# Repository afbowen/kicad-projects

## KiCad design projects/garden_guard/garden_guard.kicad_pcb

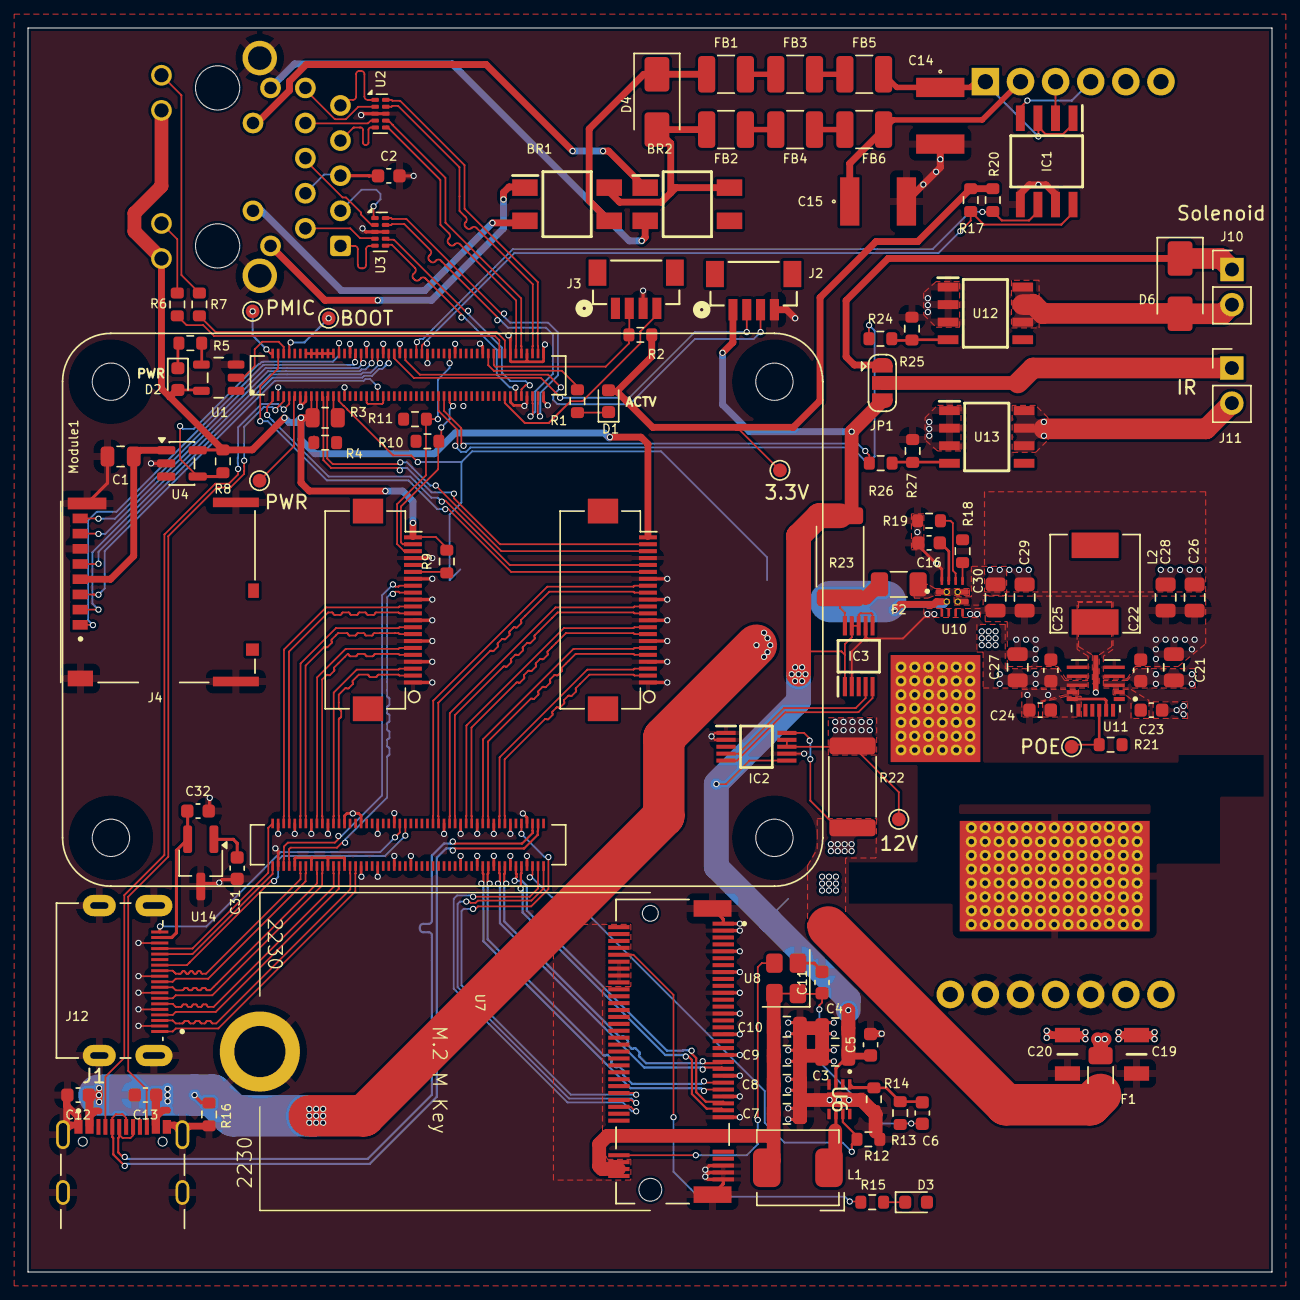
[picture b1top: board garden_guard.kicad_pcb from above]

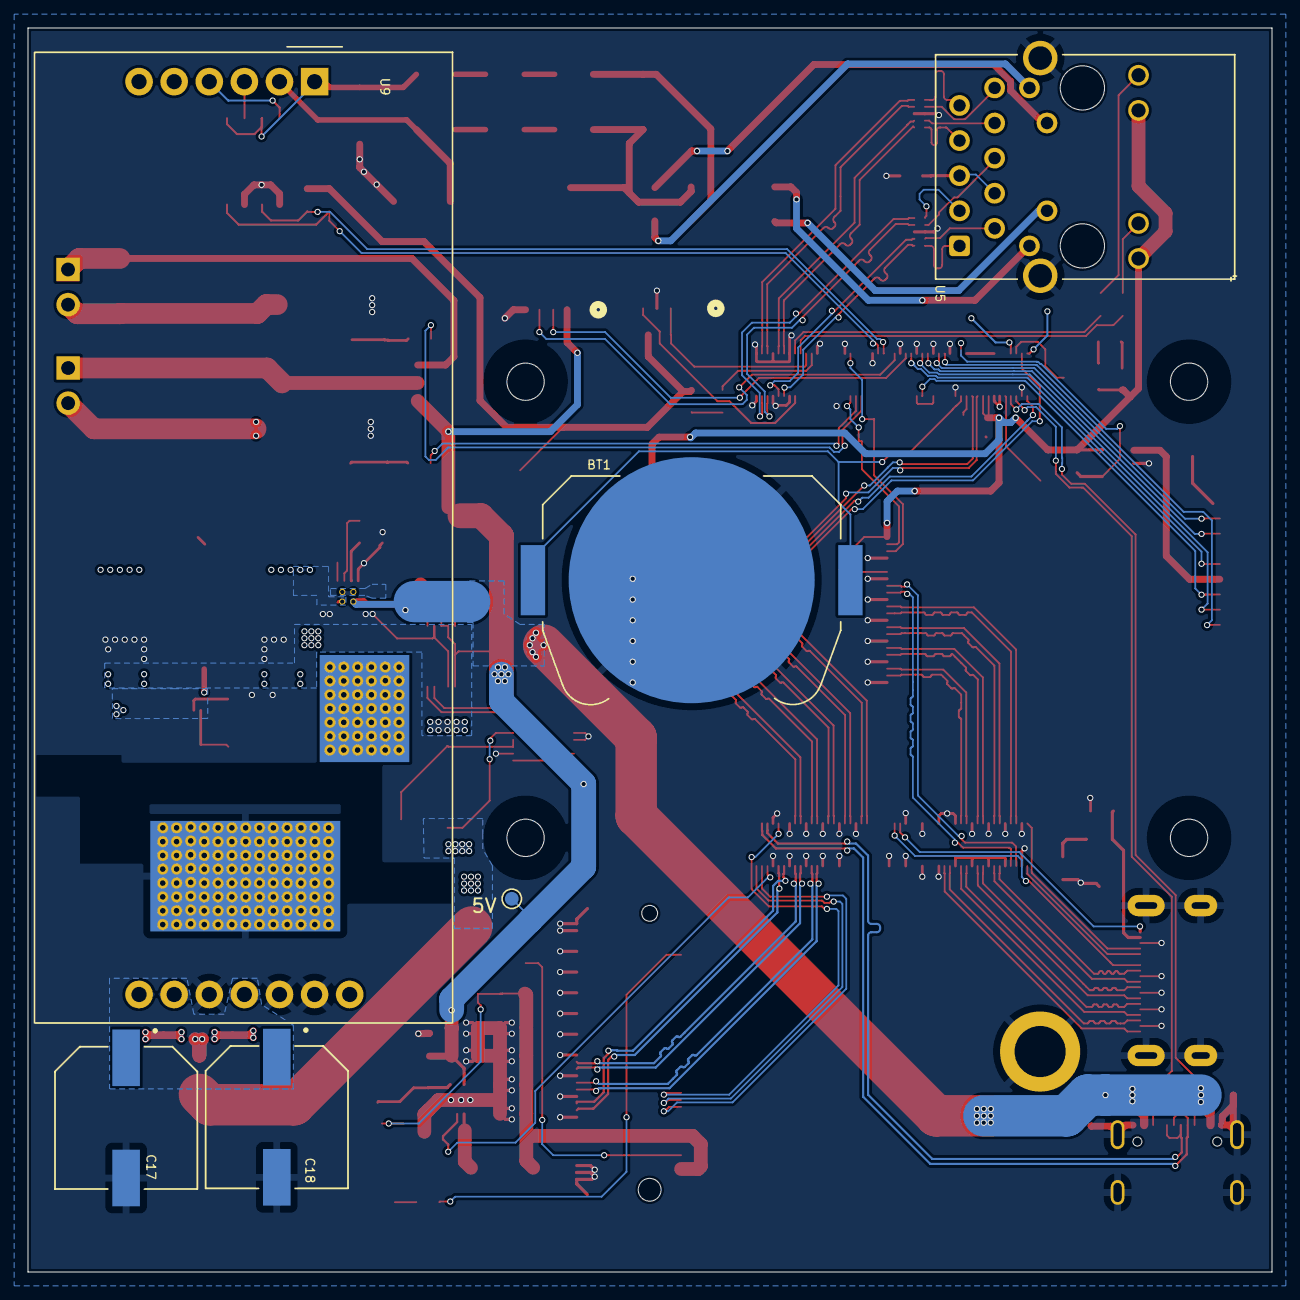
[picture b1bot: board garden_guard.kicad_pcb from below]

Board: 4 copper layers, 90.0 x 90.0 mm, 116 parts (6 on the bottom side), 140 nets.

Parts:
BR1, BR2: MB210F-MS
BT1: Battery_Cell; BatteryHolder_Keystone_3034_1x20mm
C1, C3, C4, C7, C8, C9, C10: 10uF; C_0805_2012Metric
C2, C5, C11, C12, C13, C16, C22, C23, C25, C31, C32: 0.1uF; C_0603_1608Metric
C6: 4.7nF; C_0603_1608Metric
C14, C15: 4.7nF; C1812C472KGRACAUTO
C17, C18: 1000uF; EEE-FT1E102UP
C19, C20: 10uF; CL31A106MAHNNNE
C21, C27: 4.7uF; C_0805_2012Metric
C24: 2.2uF; C_0603_1608Metric
C26, C28, C29, C30: 22uF; C_0805_2012Metric
D1, D2, D3: LED Green; LED_0603_1608Metric
D4: SMAJ58A; D_SMA
D6: SS34; D_SMA
F1, F2: 6.3A; Fuse_1206_3216Metric
FB1, FB2, FB3, FB4, FB5, FB6: 1kOhm; Fuse_1210_3225Metric
H1, H2, H3, H4: MountingHole; MountingHole_2.7mm_M2.5_DIN965
IC1: ACPL-227-50CE
IC2, IC3: INA226AQDGSRQ1
J1: SAMESKY_UJ20-C-H-G-SMT-1-P16-TR; UJ20-C-H-G-SMT-1-P16-TR
J2, J3: BM04B-SRSS-TB; BM04B-SRSS_JST
J4: Micro_SD_Card_Det; SDCARD_MOLEX_503398-1892
J5, J6: Conn_01x22_Female; Hirose_FH12-22S-0.5SH_1x22-1MP_P0.50mm_Horizontal
J10, J11: Conn_02x01; PinHeader_1x02_P2.54mm_Vertical
J12: Mini HDMI; 2013978-2
JP1: SolderJumper_3_Open; SolderJumper-3_P1.3mm_Open_RoundedPad1.0x1.5mm
L1: 2.2uH; L_Bourns_SRP5030CC
L2: SPM6550T-2R2M-HZ
Module1: ComputeModule5-CM5; Raspberry-Pi-5-Compute-Module_tall
R1, R5, R15: 1kΩ; R_0603_1608Metric
R2, R8, R13, R17, R18, R20, R21: 10kΩ; R_0603_1608Metric
R3: 0Ω; R_0805_2012Metric
R4: 0Ω; R_0603_1608Metric
R6, R7: 470Ω; R_0603_1608Metric
R9, R10, R11, R14, R16: 2.2kΩ; R_0603_1608Metric
R12, R25, R27: 100kΩ; R_0603_1608Metric
R19: 22.1k; R_0603_1608Metric
R22, R23: 5mΩ; R_2512_6332Metric
R24, R26: 100Ω; R_0603_1608Metric
TP1: BOOT; TestPoint_Pad_D1.0mm
TP2: PMIC; TestPoint_Pad_D1.0mm
TP3: PWR; TestPoint_Pad_D1.0mm
TP6: 12V; TestPoint_Pad_D1.0mm
TP7: 5V; TestPoint_Pad_D1.0mm
TP8: 3.3V; TestPoint_Pad_D1.0mm
TP9: POE; TestPoint_Pad_D1.0mm
U1: SN74LVC1G07DBVR
U2, U3: TPD4EUSB30; USON-10_2.5x1.0mm_P0.5mm
U4: RT9742GGJ5; SOT-23-5
U5: MagJack-A70-112-331N126; TRJG0926HENL
U6: AP3441SHE-7B
U7: M.2 Socket; M.2 M Key socket (2230)
U8: ASEK-32.768KHZ-L-R-T; Crystal_SMD_3225-4Pin_3.2x2.5mm
U9: Ag5810
U10: TPS2121RUXR
U11: MAX20408AFOF
U12, U13: DMN2028USS-13
U14: RT9742SNGV; TSOT-23_HandSoldering

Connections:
/+3.3v: D1.2 (A), D2.2 (A), J5.22, J6.22, Module1.84 (+3.3v_(Output)), Module1.86 (+3.3v_(Output)), R2.1, R3.1, R8.1, R9.2, R17.1, R18.1, R20.1, R21.1, TP8.1, U1.5 (VCC), U4.5 (IN), U5.15 (LEDY_A), U5.17 (LEDG_A)
/+5v: C3.1, C4.1, C5.1, C31.1, IC2.6 (VS), IC3.1 (A1), IC3.6 (VS), IC3.8 (VBUS), IC3.9 (IN-), J2.1, J3.1, JP1.3 (B), Module1.77 (+5v_(Input)), Module1.79 (+5v_(Input)), Module1.81 (+5v_(Input)), Module1.83 (+5v_(Input)), Module1.85 (+5v_(Input)), Module1.87 (+5v_(Input)), R23.2, TP7.1, U6.3 (VIN), U14.1 (IN)
/+12v: C21.1, C22.1, C25.1, C27.1, D6.1 (K), IC2.8 (VBUS), IC2.9 (IN-), J10.1, JP1.1 (A), R22.2, TP6.1, U11.1 (EN), U11.3 (SUP), U11.9 (SUP)
/CM5_GPIO (Ethernet, GPIO, MicroSD)/CAM_GPIO0: J5.17, Module1.97 (CAM_GPIO0)
/CM5_GPIO (Ethernet, GPIO, MicroSD)/CAM_GPIO1: J5.18, Module1.100 (CAM_GPIO1)
/CM5_GPIO (Ethernet, GPIO, MicroSD)/DPHY0_C_N: J5.8, Module1.127 (MIPI0_C_N)
/CM5_GPIO (Ethernet, GPIO, MicroSD)/DPHY0_C_P: J5.9, Module1.129 (MIPI0_C_P)
/CM5_GPIO (Ethernet, GPIO, MicroSD)/DPHY0_D0_N: J5.2, Module1.115 (MIPI0_D0_N)
/CM5_GPIO (Ethernet, GPIO, MicroSD)/DPHY0_D0_P: J5.3, Module1.117 (MIPI0_D0_P)
/CM5_GPIO (Ethernet, GPIO, MicroSD)/DPHY0_D1_N: J5.5, Module1.121 (MIPI0_D1_N)
/CM5_GPIO (Ethernet, GPIO, MicroSD)/DPHY0_D1_P: J5.6, Module1.123 (MIPI0_D1_P)
/CM5_GPIO (Ethernet, GPIO, MicroSD)/DPHY0_D2_N: J5.11, Module1.133 (MIPI0_D2_N)
/CM5_GPIO (Ethernet, GPIO, MicroSD)/DPHY0_D2_P: J5.12, Module1.135 (MIPI0_D2_P)
/CM5_GPIO (Ethernet, GPIO, MicroSD)/DPHY0_D3_N: J5.14, Module1.139 (MIPI0_D3_N)
/CM5_GPIO (Ethernet, GPIO, MicroSD)/DPHY0_D3_P: J5.15, Module1.141 (MIPI0_D3_P)
/CM5_GPIO (Ethernet, GPIO, MicroSD)/DPHY1_C_N: J6.8, Module1.187 (MIPI1_C_N)
/CM5_GPIO (Ethernet, GPIO, MicroSD)/DPHY1_C_P: J6.9, Module1.189 (MIPI1_C_P)
/CM5_GPIO (Ethernet, GPIO, MicroSD)/DPHY1_D0_N: J6.2, Module1.175 (MIPI1_D0_N)
/CM5_GPIO (Ethernet, GPIO, MicroSD)/DPHY1_D0_P: J6.3, Module1.177 (MIPI1_D0_P)
/CM5_GPIO (Ethernet, GPIO, MicroSD)/DPHY1_D1_N: J6.5, Module1.181 (MIPI1_D1_N)
/CM5_GPIO (Ethernet, GPIO, MicroSD)/DPHY1_D1_P: J6.6, Module1.183 (MIPI1_D1_P)
/CM5_GPIO (Ethernet, GPIO, MicroSD)/DPHY1_D2_N: J6.11, Module1.193 (MIPI1_D2_N)
/CM5_GPIO (Ethernet, GPIO, MicroSD)/DPHY1_D2_P: J6.12, Module1.195 (MIPI1_D2_P)
/CM5_GPIO (Ethernet, GPIO, MicroSD)/DPHY1_D3_N: J6.14, Module1.194 (MIPI1_D3_N)
/CM5_GPIO (Ethernet, GPIO, MicroSD)/DPHY1_D3_P: J6.15, Module1.196 (MIPI1_D3_P)
/CM5_GPIO (Ethernet, GPIO, MicroSD)/HDMI0_CEC: J12.13 (CEC), Module1.151 (HDMI0_CEC)
/CM5_GPIO (Ethernet, GPIO, MicroSD)/HDMI0_CK_N: J12.12 (CK-), Module1.190 (HDMI0_CLK_N)
/CM5_GPIO (Ethernet, GPIO, MicroSD)/HDMI0_CK_P: J12.10 (CK+), Module1.188 (HDMI0_CLK_P)
/CM5_GPIO (Ethernet, GPIO, MicroSD)/HDMI0_D0_N: J12.9 (D0-), Module1.184 (HDMI0_TX0_N)
/CM5_GPIO (Ethernet, GPIO, MicroSD)/HDMI0_D0_P: J12.7 (D0+), Module1.182 (HDMI0_TX0_P)
/CM5_GPIO (Ethernet, GPIO, MicroSD)/HDMI0_D1_N: J12.6 (D1-), Module1.178 (HDMI0_TX1_N)
/CM5_GPIO (Ethernet, GPIO, MicroSD)/HDMI0_D1_P: J12.4 (D1+), Module1.176 (HDMI0_TX1_P)
/CM5_GPIO (Ethernet, GPIO, MicroSD)/HDMI0_D2_N: J12.3 (D2-), Module1.172 (HDMI0_TX2_N)
/CM5_GPIO (Ethernet, GPIO, MicroSD)/HDMI0_D2_P: J12.1 (D2+), Module1.170 (HDMI0_TX2_P)
/CM5_GPIO (Ethernet, GPIO, MicroSD)/HDMI0_HOTPLUG: J12.19 (HPD/HEAC-), Module1.153 (HDMI0_HOTPLUG)
/CM5_GPIO (Ethernet, GPIO, MicroSD)/HDMI0_SCL: J12.15 (SCL), Module1.200 (HDMI0_SCL)
/CM5_GPIO (Ethernet, GPIO, MicroSD)/HDMI0_SDA: J12.16 (SDA), Module1.199 (HDMI0_SDA)
/CM5_GPIO (Ethernet, GPIO, MicroSD)/HDMI_5v: C32.1, J12.18 (+5V), U14.2 (OUT)
/CM5_GPIO (Ethernet, GPIO, MicroSD)/ID_SC: J6.20, Module1.35 (ID_SC), R11.2
/CM5_GPIO (Ethernet, GPIO, MicroSD)/ID_SD: J6.21, Module1.36 (ID_SD), R10.2
/CM5_GPIO (Ethernet, GPIO, MicroSD)/PCIE_CLK_N: Module1.112 (PCIe_CLK_N), U7.53 (REFCLKn)
/CM5_GPIO (Ethernet, GPIO, MicroSD)/PCIE_CLK_P: Module1.110 (PCIe_CLK_P), U7.55 (REFCLKp)
/CM5_GPIO (Ethernet, GPIO, MicroSD)/PCIE_PWR_EN: Module1.106 (PCIE_PWR_EN), R12.1, U6.7 (EN)
/CM5_GPIO (Ethernet, GPIO, MicroSD)/PCIE_RX_N: Module1.118 (PCIe_RX_N), U7.43 (PETp0)
/CM5_GPIO (Ethernet, GPIO, MicroSD)/PCIE_RX_P: Module1.116 (PCIe_RX_P), U7.41 (PETn0)
/CM5_GPIO (Ethernet, GPIO, MicroSD)/PCIE_TX_N: Module1.124 (PCIe_TX_N), U7.49 (PERp0)
/CM5_GPIO (Ethernet, GPIO, MicroSD)/PCIE_TX_P: Module1.122 (PCIe_TX_P), U7.47 (PERn0)
/CM5_GPIO (Ethernet, GPIO, MicroSD)/PCIE_nCLKREQ: Module1.102 (PCIe_nCLKREQ), U7.52 (~CLKREQ)
/CM5_GPIO (Ethernet, GPIO, MicroSD)/PCIE_nRST: Module1.109 (PCIe_nRST), U7.50 (~PERST)
/CM5_GPIO (Ethernet, GPIO, MicroSD)/PCIE_nWAKE: Module1.104 (PCIE_nWAKE), U7.54 (~PEWAKE)
/CM5_GPIO (Ethernet, GPIO, MicroSD)/SCL0: J5.20, Module1.80 (SCL0)
/CM5_GPIO (Ethernet, GPIO, MicroSD)/SDA0: J5.21, Module1.82 (SDA0)
/CM5_HighSpeed/5V_PWR_ALERT: IC3.3 (ALERT), Module1.39 (GPIO8)
/CM5_HighSpeed/12V_PWR_ALERT: IC2.3 (ALERT), Module1.37 (GPIO7)
/CM5_HighSpeed/+1.8v: Module1.88 (+1.8v_(Output)), Module1.90 (+1.8v_(Output)), R4.1
/CM5_HighSpeed/CC1: J1.A5 (CC1), Module1.94 (CC1)
/CM5_HighSpeed/CC2: J1.B5 (CC2), Module1.96 (CC2)
/CM5_HighSpeed/ETH_LEDG: Module1.17 (Ethernet_nLED2(3.3v)), R6.1
/CM5_HighSpeed/ETH_LEDY: Module1.15 (Ethernet_nLED3(3.3v)), R7.1
/CM5_HighSpeed/FAN_PWM: J3.2, Module1.19 (FAN_PWM), R2.2
/CM5_HighSpeed/GPIO_VREF: Module1.78 (GPIO_VREF(1.8v/3.3v_Input)), R3.2, R4.2, R10.1, R11.1
/CM5_HighSpeed/IR_ILLUM_EN: Module1.38 (GPIO11), R26.2
/CM5_HighSpeed/PMIC_ENABLE: Module1.99 (PMIC_ENABLE), TP2.1
/CM5_HighSpeed/PWR_BUT: Module1.92 (PWR_BUT), TP3.1
/CM5_HighSpeed/PWR_SRC_ST: Module1.41 (GPIO25), R18.2, U10.9 (ST)
/CM5_HighSpeed/PoE++_actv: IC1.6 (COLLECTOR_1), Module1.47 (GPIO23), R20.2
/CM5_HighSpeed/PoE+_actv: IC1.8 (COLLECTOR_2), Module1.45 (GPIO24), R17.2
/CM5_HighSpeed/SD_CLK: J4.5 (CLK), Module1.57 (SD_CLK)
/CM5_HighSpeed/SD_CMD: J4.3 (CMD), Module1.62 (SD_CMD)
/CM5_HighSpeed/SD_DAT0: J4.7 (DAT0), Module1.63 (SD_DAT0)
/CM5_HighSpeed/SD_DAT1: J4.8 (DAT1), Module1.67 (SD_DAT1)
/CM5_HighSpeed/SD_DAT2: J4.1 (DAT2), Module1.69 (SD_DAT2)
/CM5_HighSpeed/SD_DAT3: J4.2 (DAT3/CD), Module1.61 (SD_DAT3)
/CM5_HighSpeed/SD_PWR: C1.1, J4.4 (VDD), U4.1 (OUT)
/CM5_HighSpeed/SD_PWR_ON: Module1.75 (SD_PWR_ON), R8.2, U4.4 (EN)
/CM5_HighSpeed/SOLENOID_EN: Module1.40 (GPIO9), R24.1
/CM5_HighSpeed/TACHO: J3.4, Module1.16 (FAN_TACHO)
/CM5_HighSpeed/TR0_TAP: BR1.1 (~_1), U5.11 (VC1)
/CM5_HighSpeed/TR1_TAP: BR1.2 (~_2), U5.12 (VC2)
/CM5_HighSpeed/TR2_TAP: BR2.1 (~_1), U5.13 (VC3)
/CM5_HighSpeed/TR3_TAP: BR2.2 (~_2), U5.14 (VC4)
/CM5_HighSpeed/TRD0_N: Module1.10 (Ethernet_Pair0_N), U3.4 (D2+), U3.7, U5.2 (TRD0-)
/CM5_HighSpeed/TRD0_P: Module1.12 (Ethernet_Pair0_P), U3.5 (D2-), U3.6, U5.1 (TRD0+)
/CM5_HighSpeed/TRD1_N: Module1.6 (Ethernet_Pair1_N), U3.2 (D1-), U3.9, U5.6 (TRD1-)
/CM5_HighSpeed/TRD1_P: Module1.4 (Ethernet_Pair1_P), U3.1 (D1+), U3.10, U5.3 (TRD1+)
/CM5_HighSpeed/TRD2_N: Module1.9 (Ethernet_Pair2_N), U2.4 (D2+), U2.7, U5.8 (TRD2-)
/CM5_HighSpeed/TRD2_P: Module1.11 (Ethernet_Pair2_P), U2.5 (D2-), U2.6, U5.7 (TRD2+)
/CM5_HighSpeed/TRD3_N: Module1.5 (Ethernet_Pair3_N), U2.2 (D1-), U2.9, U5.10 (TRD3-)
/CM5_HighSpeed/TRD3_P: Module1.3 (Ethernet_Pair3_P), U2.1 (D1+), U2.10, U5.9 (TRD3+)
/CM5_HighSpeed/UART0_RX: J2.3, Module1.51 (GPIO15)
/CM5_HighSpeed/UART0_TX: J2.2, Module1.55 (GPIO14)
/CM5_HighSpeed/VBAT: BT1.1 (+), Module1.76 (VBAT)
/CM5_HighSpeed/nPWR_LED: Module1.95 (LED_nPWR), U1.2 (A)
/CM5_HighSpeed/nRPIBOOT: Module1.93 (nRPIBOOT), TP1.1
/PCIe-M2/FB: C6.2, R13.2, R14.1, U6.1 (FB)
/PCIe-M2/M2_3v3: C6.1, C7.1, C8.1, C9.1, C10.1, C11.1, D3.2 (A), L1.2, R13.1, U7.2 (3.3V), U7.4 (3.3V), U7.12 (3.3V), U7.14 (3.3V), U7.16 (3.3V), U7.18 (3.3V), U7.70 (3.3V), U7.72 (3.3V), U7.74 (3.3V), U8.1 (EN), U8.4 (VDD)
/Peripherals/IR_ILLUM+: J11.1, JP1.2 (C)
/Peripherals/IR_ILLUM-: J11.2, U13.5 (D_1), U13.6 (D_2), U13.7 (D_3), U13.8 (D_4)
/Peripherals/SOLENOID-: D6.2 (A), J10.2, U12.5 (D_1), U12.6 (D_2), U12.7 (D_3), U12.8 (D_4)
/Power/+5v_poe: C26.1, C28.1, C29.1, C30.1, L2.1, U10.7 (IN1), U11.13 (OUT)
/Power/+5v_pre_shunt: F2.2, IC3.10 (IN+), R23.1
/Power/+5v_usb: C12.1, C13.1, J1.A4_B9 (VBUS), J1.B4_A9 (VBUS__1), R16.1, U10.2 (IN2)
/Power/+12v_pre_shunt: F1.2, IC2.10 (IN+), R22.1
/Power/LX: C23.1, L2.2, U11.6 (LX)
/Power/SCL1: IC2.5 (SCL), IC3.5 (SCL), Module1.58 (GPIO2)
/Power/SDA1: IC2.4 (SDA), IC3.4 (SDA), Module1.56 (GPIO3)
/USB2_N: J1.A7 (D-), J1.B7 (D-), Module1.103 (USB2_N)
/USB2_P: J1.A6 (D+), J1.B6 (D+), Module1.105 (USB2_P)
GND: BT1.2 (-), C1.2, C2.2, C3.2, C4.2, C5.2, C7.2, C8.2, C9.2, C10.2, C11.2, C12.2, C13.2, C14.2, C15.2, C16.2, C17.2, C18.2, C19.2, C20.2, C21.2, C22.2, C24.2, C25.2, C26.2, C27.2, C28.2, C29.2, C30.2, C31.2, C32.2, IC1.5 (EMITTER_1), IC1.7 (EMITTER_2), IC2.1 (A1), IC2.2 (A0), IC2.7 (GND), IC3.2 (A0), IC3.7 (GND), J1.A1_B12 (GND), J1.B1_A12 (GND__1), J1.SH1 (SHIELD), J1.SH2 (SHIELD__1), J1.SH3 (SHIELD__2), J1.SH4 (SHIELD__3), J2.4, J3.3, J4.6 (VSS), J4.11 (SHIELD), J5.1, J5.4, J5.7, J5.10, J5.13, J5.16, J5.19, J6.1, J6.4, J6.7, J6.10, J6.13, J6.16, J6.19, J12.2 (D2S), J12.5 (D1S), J12.8 (D0S), J12.11 (CKS), J12.17 (GND), J12.SH1 (SH), J12.SH2 (SH), J12.SH3 (SH), J12.SH4 (SH), Module1.1 (GND), Module1.2 (GND), Module1.7 (GND), Module1.8 (GND), Module1.13 (GND), Module1.14 (GND), Module1.22 (GND), Module1.23 (GND), Module1.32 (GND), Module1.33 (GND), Module1.42 (GND), Module1.43 (GND), Module1.52 (GND), Module1.53 (GND), Module1.59 (GND), Module1.60 (GND), Module1.65 (GND), Module1.66 (GND), Module1.71 (GND), Module1.74 (GND), Module1.98 (GND), Module1.107 (GND), Module1.108 (GND), Module1.113 (GND), Module1.114 (GND), Module1.119 (GND), Module1.120 (GND), Module1.125 (GND), Module1.126 (GND), Module1.131 (GND), Module1.132 (GND), Module1.137 (GND), Module1.138 (GND), Module1.144 (GND), Module1.150 (GND), Module1.155 (GND), Module1.156 (GND), Module1.161 (GND), Module1.162 (GND), Module1.167 (GND), Module1.168 (GND), Module1.173 (GND), Module1.174 (GND), Module1.179 (GND), Module1.180 (GND), Module1.185 (GND), Module1.186 (GND), Module1.191 (GND), Module1.192 (GND), Module1.197 (GND), Module1.198 (GND), R12.2, R14.2, R16.2, R19.2, R25.2, R27.2, U1.3 (GND), U2.3 (GND), U2.8 (GND), U3.3 (GND), U3.8 (GND), U4.2 (GND), U5.19 (SHIELD), U5.20 (SHIELD), U6.4 (PGND), U6.8 (SGND), U6.9 (PAD), U7.1 (GND), U7.3 (GND), U7.9 (GND), U7.15 (GND), U7.21 (GND), U7.27 (GND), U7.33 (GND), U7.39 (GND), U7.45 (GND), U7.51 (GND), U7.57 (GND), U7.71 (GND), U7.73 (GND), U7.75 (GND), U7.M1 (GND2230), U7.S1, U7.S2, U8.2 (GND), U9.9 (0v1), U9.11 (0V2), U9.12 (0V2), U10.3 (CP2), U10.4 (OV2), U10.5 (OV1), U10.6 (PR1), U10.12 (GND), U11.4 (PGND), U11.5 (PGND), U11.7 (PGND), U11.8 (PGND), U11.10 (GND), U12.1 (S_1), U12.2 (S_2), U12.3 (S_3), U13.1 (S_1), U13.2 (S_2), U13.3 (S_3), U14.3 (GND)
unnamed: BR1.3 (+), BR2.3 (+), D4.1 (A1), FB1.1
unnamed: BR1.4 (-), BR2.4 (-), D4.2 (A2), FB2.1
unnamed: C2.1, U5.4 (CT), U5.5 (CT)
unnamed: D1.1 (K), R1.1
unnamed: D2.1 (K), R5.1
unnamed: D3.1 (K), R15.1
unnamed: F2.1, U10.1 (OUT), U10.8 (OUT)
unnamed: FB1.2, FB3.1
unnamed: FB2.2, FB4.1
unnamed: FB3.2, FB5.1
unnamed: FB4.2, FB6.1
unnamed: C14.1, FB5.2, IC1.1 (ANODE_1), IC1.3 (ANODE_2), U9.1 (VIN+)
unnamed: IC1.2 (CATHODE_1), U9.3 (TYP2-DET)
unnamed: IC1.4 (CATHODE_2), U9.4 (TYP4-DET)
unnamed: J6.17, R9.1
unnamed: Module1.21 (LED_nACT), R1.2
unnamed: R5.2, U1.4 (Y)
unnamed: R7.2, U5.18 (LEDG_K)
unnamed: R6.2, U5.16 (LEDY_K)
unnamed: L1.1, U6.6 (LX)
unnamed: R15.2, U7.10 (DAS/~DSS/~LED1)
unnamed: U7.68 (SUSCLK), U8.3 (Out)
unnamed: C15.1, FB6.2, U9.2 (VIN-)
unnamed: C17.1, C18.1, C19.1, C20.1, F1.1, U9.7 (VOUT1), U9.8 (VOUT1), U9.10 (VOUT2)
unnamed: R19.1, U10.10 (ILIM)
unnamed: C16.1, U10.11 (SS)
unnamed: C24.1, U11.11 (BIAS), U11.12 (FB), U11.16 (SYNC)
unnamed: C23.2, U11.2 (BST)
unnamed: R21.2, TP9.1, U11.15 (PGOOD)
unnamed: R24.2, R25.1, U12.4 (G)
unnamed: R26.1, R27.1, U13.4 (G)
